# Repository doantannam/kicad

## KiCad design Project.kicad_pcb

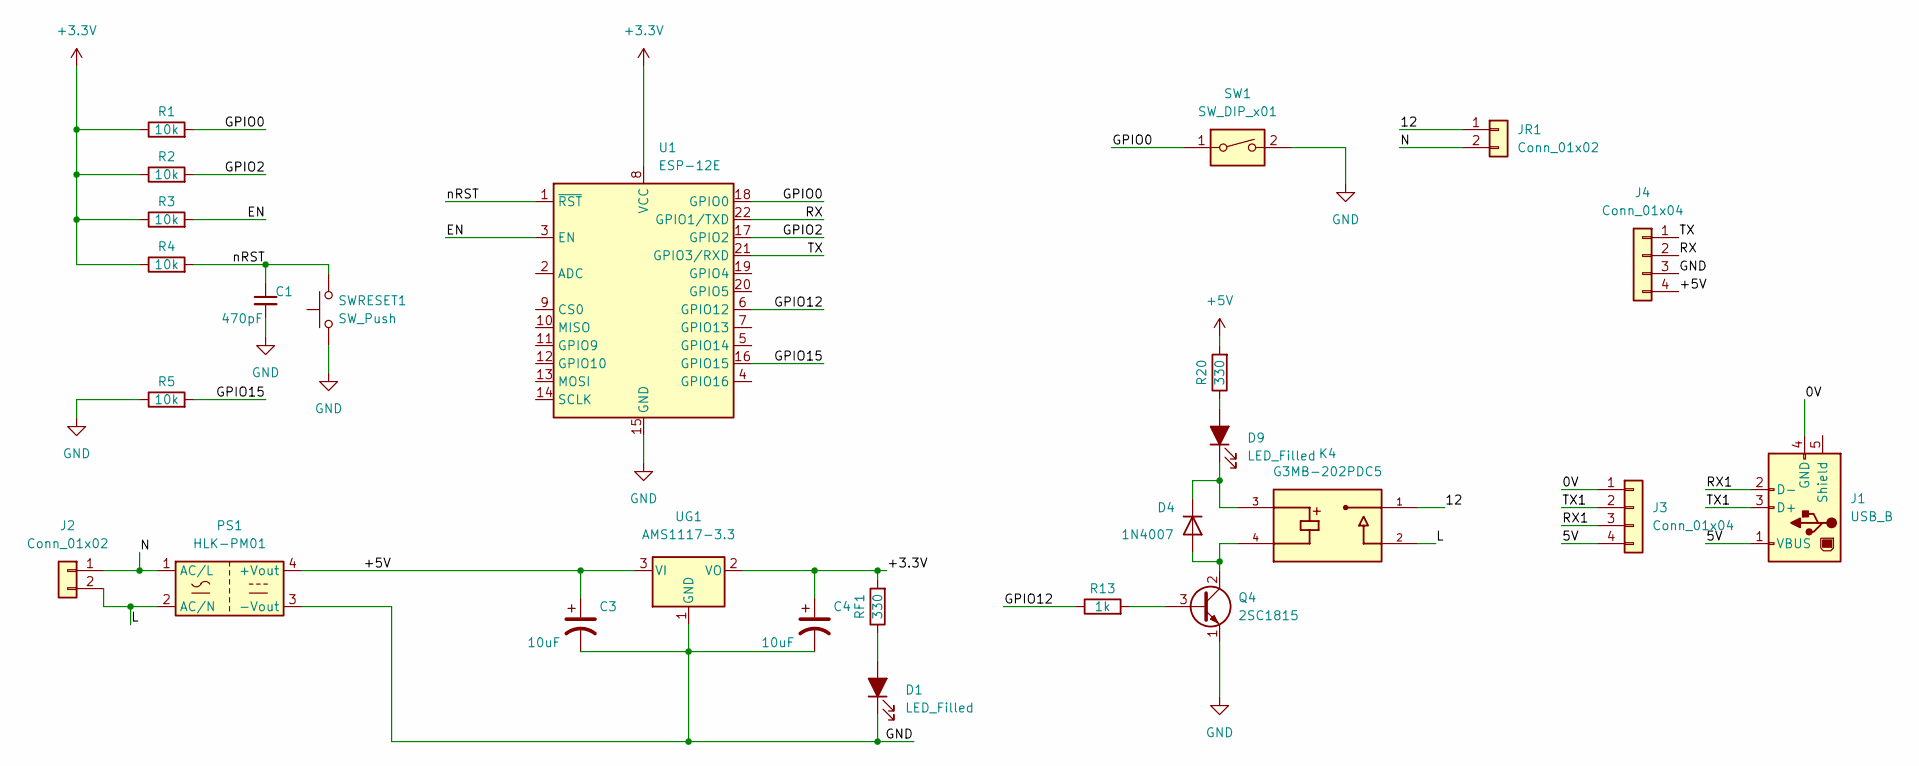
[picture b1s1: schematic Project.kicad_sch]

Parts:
C1: 470pF; C_Disc_D5.0mm_W2.5mm_P5.00mm
C3, C4: 10uF; CP_Radial_D5.0mm_P2.50mm
D1, D9: LED_Filled; LED_D3.0mm
D4: 1N4007; D_DO-41_SOD81_P10.16mm_Horizontal
J1: USB_B; USB_B_Lumberg_2411_02_Horizontal
J2: Conn_01x02; PhoenixContact_MC_1,5_2-G-3.81_1x02_P3.81mm_Horizontal
J3, J4: Conn_01x04; PinSocket_1x04_P2.54mm_Vertical
JR1: Conn_01x02; PhoenixContact_MC_1,5_2-G-3.81_1x02_P3.81mm_Horizontal
K4: G3MB-202PDC5; RELAY_G3MB-202PDC5; PARTREV J091-E1-1A
PS1: HLK-PM01; Converter_ACDC_HiLink_HLK-PMxx
Q4: 2SC1815; TO-92_Inline
R1, R2, R3, R4, R5: 10k; R_Axial_DIN0207_L6.3mm_D2.5mm_P10.16mm_Horizontal
R13: 1k; R_Axial_DIN0207_L6.3mm_D2.5mm_P10.16mm_Horizontal
R20: 330; R_Axial_DIN0207_L6.3mm_D2.5mm_P10.16mm_Horizontal
RF1: 330; R_Axial_DIN0207_L6.3mm_D2.5mm_P10.16mm_Horizontal
SW1: SW_DIP_x01; PinHeader_1x02_P2.54mm_Vertical
SWRESET1: SW_Push; SW_Tactile_SPST_Angled_PTS645Vx39-2LFS
U1: ESP-12E
UG1: AMS1117-3.3; SOT-223-3_TabPin2

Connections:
+3.3V: C4.1, R1.1, R2.1, R3.1, R4.1, RF1.2, U1.8 (VCC), UG1.2 (VO)
+5V: C3.1, J4.4, PS1.4 (+Vout), R20.2, UG1.3 (VI)
/0V: J1.4 (GND), J3.1
/5V: J1.1 (VBUS), J3.4
/12: JR1.1, K4.1
/EN: R3.2, U1.3 (EN)
/GPIO0: R1.2, SW1.1, U1.18 (GPIO0)
/GPIO2: R2.2, U1.17 (GPIO2)
/GPIO12: R13.1, U1.6 (GPIO12)
/GPIO15: R5.2, U1.16 (GPIO15)
/L: J2.2, K4.2, PS1.2 (AC/N)
/N: J2.1, JR1.2, PS1.1 (AC/L)
/RX: J4.2, U1.22 (GPIO1/TXD)
/RX1: J1.2 (D-), J3.3
/TX: J4.1, U1.21 (GPIO3/RXD)
/TX1: J1.3 (D+), J3.2
/nRST: C1.1, R4.2, SWRESET1.1, U1.1 (~RST)
GND: C1.2, C3.2, C4.2, D1.1 (K), J4.3, PS1.3 (-Vout), Q4.1 (E), R5.1, SW1.2, SWRESET1.2, U1.15 (GND), UG1.1 (GND)
unnamed: D1.2 (A), RF1.1
unnamed: D4.1 (K), D9.1 (K), K4.3
unnamed: D4.2 (A), K4.4, Q4.2 (C)
unnamed: D9.2 (A), R20.1
unnamed: Q4.3 (B), R13.2

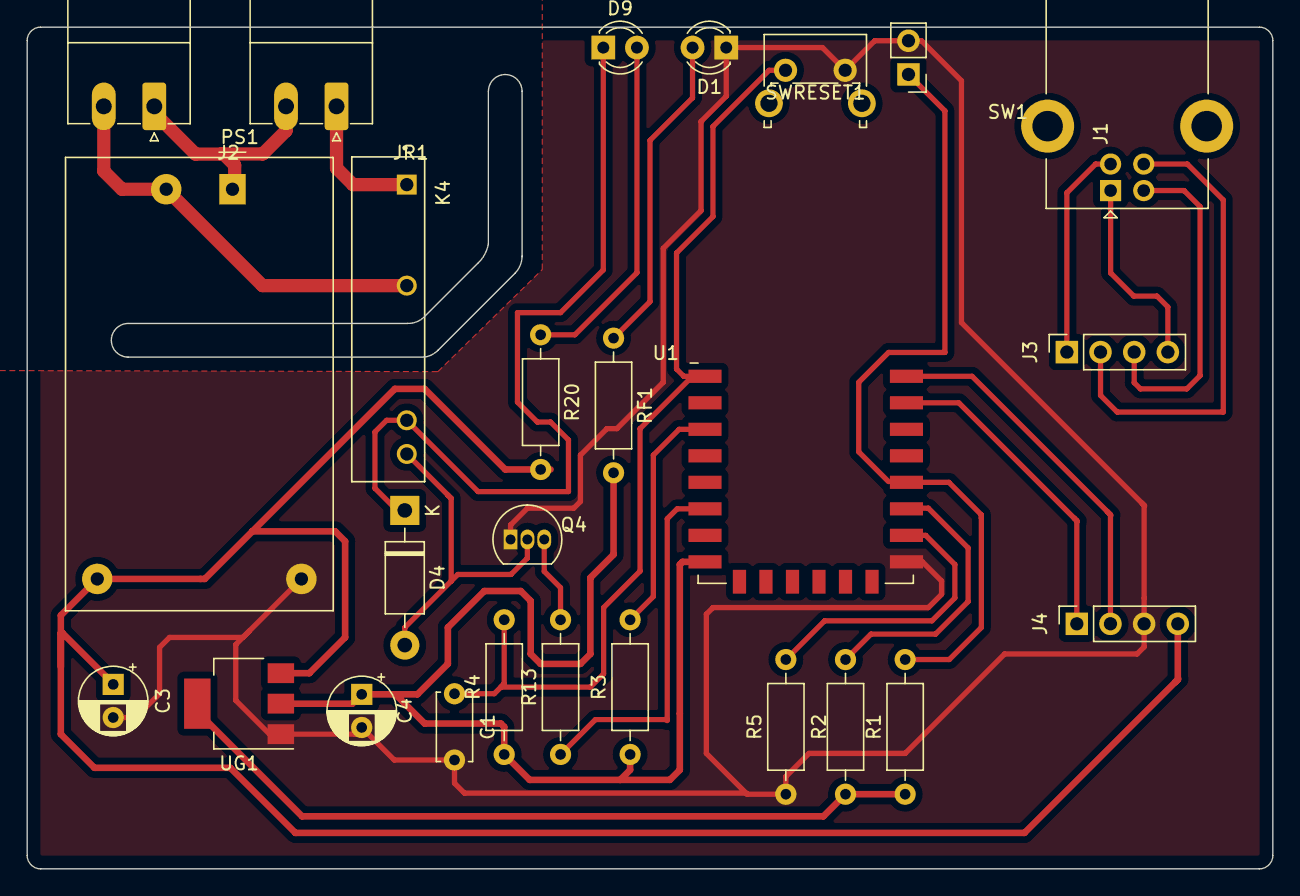
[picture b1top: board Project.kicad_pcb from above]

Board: 2 copper layers, 94.0 x 63.5 mm, 26 parts (0 on the bottom side), 23 nets.

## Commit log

2022-11-04 save code
2022-12-05 change
2022-12-06 Add new modifier
